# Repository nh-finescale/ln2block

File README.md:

# ln2block

ln2block is the combination of hardware and software to send block messages in a Fremo meeting between two block enabled stations. There are more implementations for this, which can be found at [fremo-block](http://fremo-block.sourceforge.net/) The ln2block variant aims to directly connect Loconet switchpanels to block. First implementation is done with https://smf-modelle.de/ Dr-S2 panels in the Loconet variant. But other implementations such as arduino based or felderblock are possible.

## hardware

The hardware is a adaption of the boards shown [here](http://fremo-block.sourceforge.net/Loconet2Block/index.html) with the following adaptations:
- Schlüesselinterface integrated
- Arduino Nano based to ease programming and debugging
- OLED status display

v5 is a variant which has connections on both ends of the pcb.

v6 is adapted to fit the Strapubox SP2000 (again).

## Getting parts:

Reichelt Shopping Cart for V5 parts: (https://www.reichelt.de/my/1871884). For logging purposes a SSD1306 OLED Display is used. Any I2C variant should work.

## Manuals:

See [the wiki](https://github.com/nh-finescale/ln2block/wiki)

## Software

Software is fully functional for:
* Tf71
* Relaisblock
* Felderblock

### Programming the Arduino

To program the Arduino please use the Arduino IDE.

#### Prerequisites:
* Wire Library (included within IDE): needed for the U8g2 Library
* U8g2 Library: to write text and/or graphic on the OLED display
* LocoNet Library: to send/receive Loconet messages

## Configuration

The ln2block software can be configured through LNCV programming. The values in scope are described at [fremo-block](http://fremo-block.sourceforge.net/Loconet2Block/config.html).
A spreadsheet to calculate the appropriate values for each LNCV is found at https://github.com/nh-finescale/ln2block/tree/main/documentation

This sheet also contains a HEX explanation to translate HEX values shown on the OLED display back into which LNCV are on and off.

## Module connectivity

todo

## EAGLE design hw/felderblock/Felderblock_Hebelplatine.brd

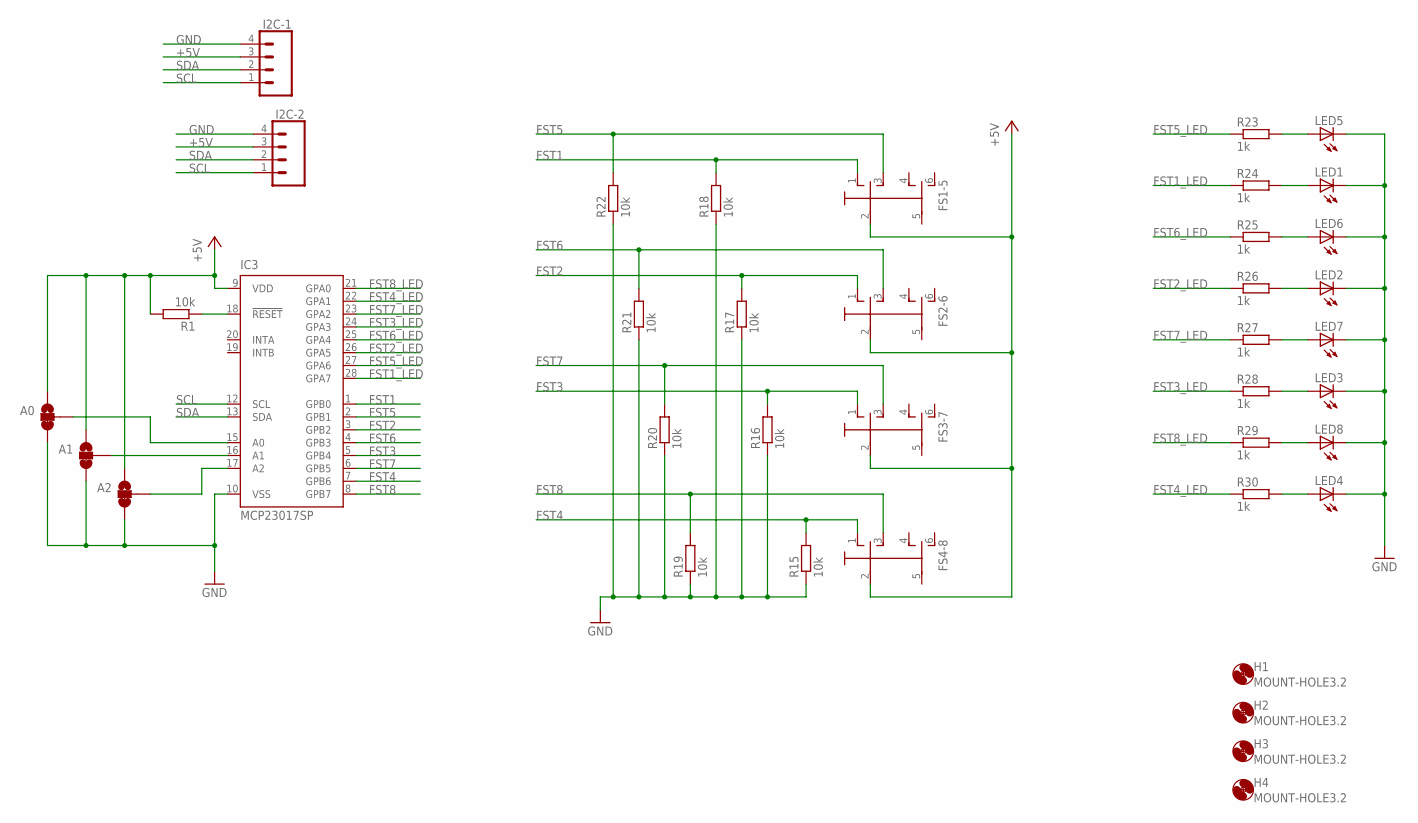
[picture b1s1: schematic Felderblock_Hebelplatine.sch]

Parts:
A0, A1, A2: JUMPER-SMT_3_1-NC_TRACE_SILK; SMT-JUMPER_3_1-NC_TRACE_SILK
FS1-5, FS2-6, FS3-7, FS4-8: SW_2POL_ON-OFF-ONSOLDERPAD; DIL6_LARGE
H1, H2, H3, H4: MOUNT-HOLE3.2; 3,2
I2C-1, I2C-2: CONN_04JST-PTH-VERT; JST-4-PTH-VERT
IC3: MCP23017SP; DIL28-3
LED1, LED2, LED3, LED4, LED5, LED6, LED7, LED8: LED3MM
R1, R15, R16, R17, R18, R19, R20, R21, R22: 10k; 0207/7
R23, R24, R25, R26, R27, R28, R29, R30: 1k; 0207/7

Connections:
+5V: A0.1, A1.1, A2.1, FS1-5.2, FS2-6.2, FS3-7.2, FS4-8.2, I2C-1.3, I2C-2.3, IC3.9 (VDD), R1.2
FST1: FS1-5.1 (O), IC3.1 (GPB0), R18.2
FST1_LED: IC3.28 (GPA7), R24.1
FST2: FS2-6.1 (O), IC3.3 (GPB2), R17.2
FST2_LED: IC3.26 (GPA5), R26.1
FST3: FS3-7.1 (O), IC3.5 (GPB4), R16.2
FST3_LED: IC3.24 (GPA3), R28.1
FST4: FS4-8.1 (O), IC3.7 (GPB6), R15.2
FST4_LED: IC3.22 (GPA1), R30.1
FST5: FS1-5.3 (S), IC3.2 (GPB1), R22.2
FST5_LED: IC3.27 (GPA6), R23.1
FST6: FS2-6.3 (S), IC3.4 (GPB3), R21.2
FST6_LED: IC3.25 (GPA4), R25.1
FST7: FS3-7.3 (S), IC3.6 (GPB5), R20.2
FST7_LED: IC3.23 (GPA2), R27.1
FST8: FS4-8.3 (S), IC3.8 (GPB7), R19.2
FST8_LED: IC3.21 (GPA0), R29.1
GND: A0.3, A1.3, A2.3, I2C-1.4, I2C-2.4, IC3.10 (VSS), LED1.K (C), LED2.K (C), LED3.K (C), LED4.K (C), LED5.K (C), LED6.K (C), LED7.K (C), LED8.K (C), R15.1, R16.1, R17.1, R18.1, R19.1, R20.1, R21.1, R22.1
unnamed: A0.2, IC3.15 (A0)
unnamed: A2.2, IC3.17 (A2)
unnamed: A1.2, IC3.16 (A1)
unnamed: IC3.18 (!RESET), R1.1
unnamed: LED5.A, R23.2
unnamed: LED1.A, R24.2
unnamed: LED6.A, R25.2
unnamed: LED2.A, R26.2
unnamed: LED7.A, R27.2
unnamed: LED3.A, R28.2
unnamed: LED8.A, R29.2
unnamed: LED4.A, R30.2
SCL: I2C-1.1, I2C-2.1, IC3.12 (SCL)
SDA: I2C-1.2, I2C-2.2, IC3.13 (SDA)

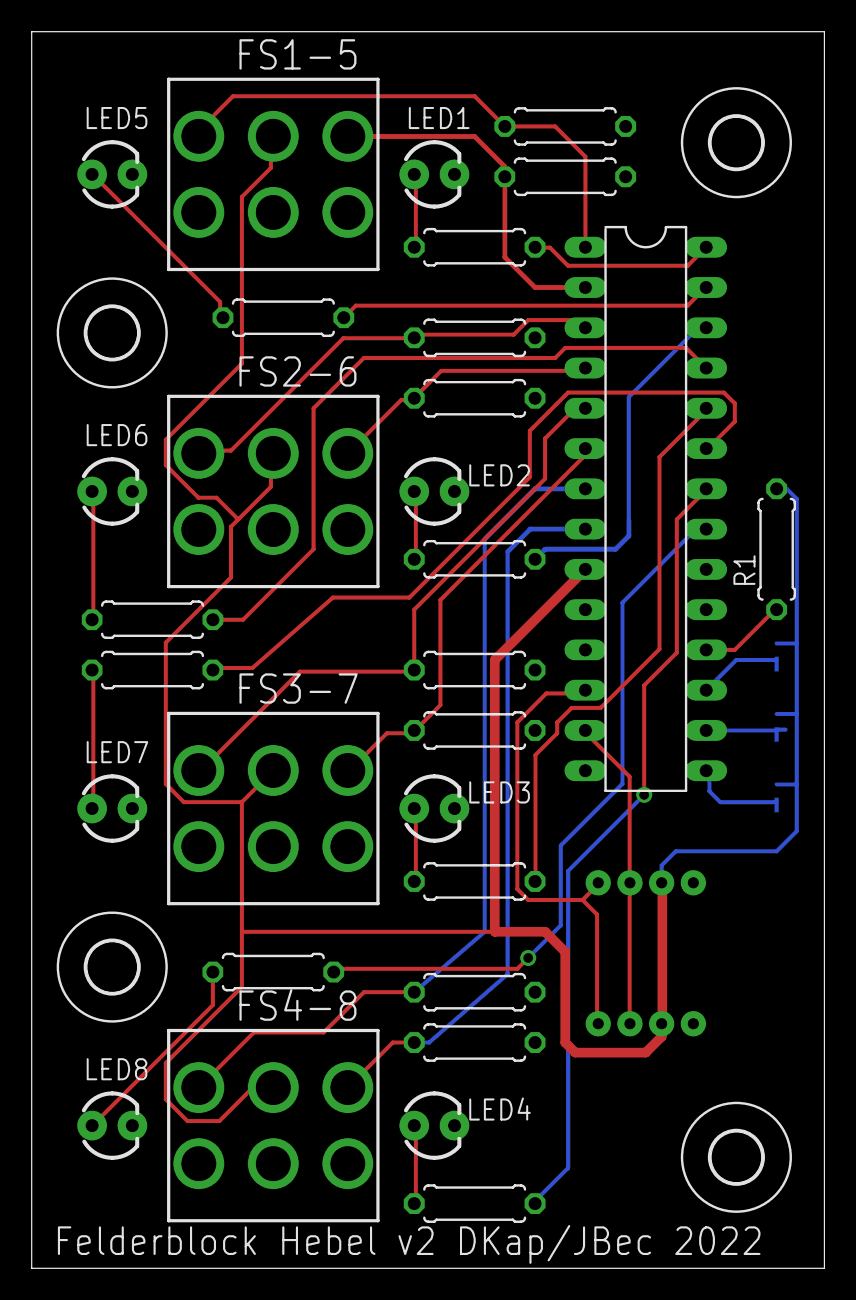
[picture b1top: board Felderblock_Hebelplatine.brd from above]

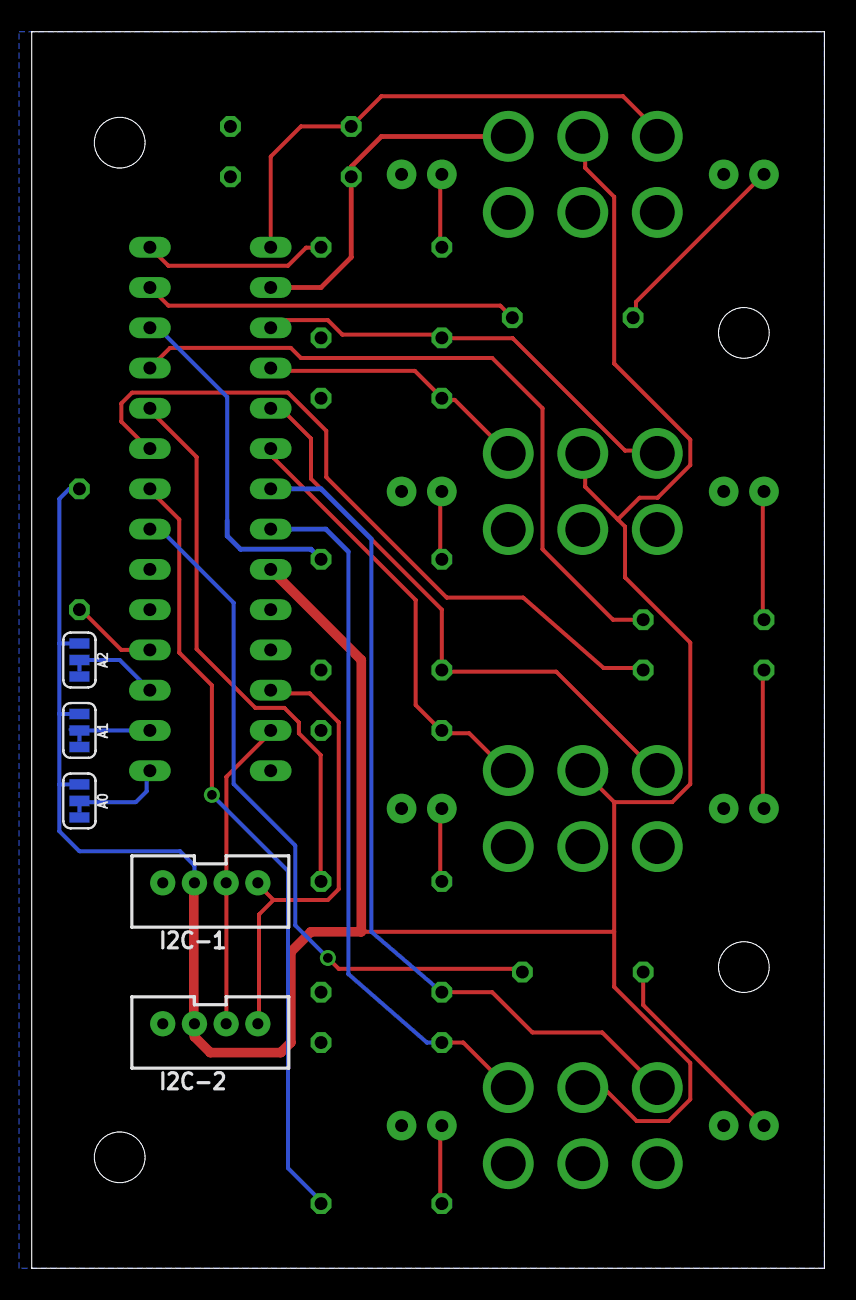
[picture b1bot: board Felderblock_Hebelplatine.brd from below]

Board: 2 copper layers, 50.0 x 78.0 mm, 39 parts (5 on the bottom side), 32 nets.

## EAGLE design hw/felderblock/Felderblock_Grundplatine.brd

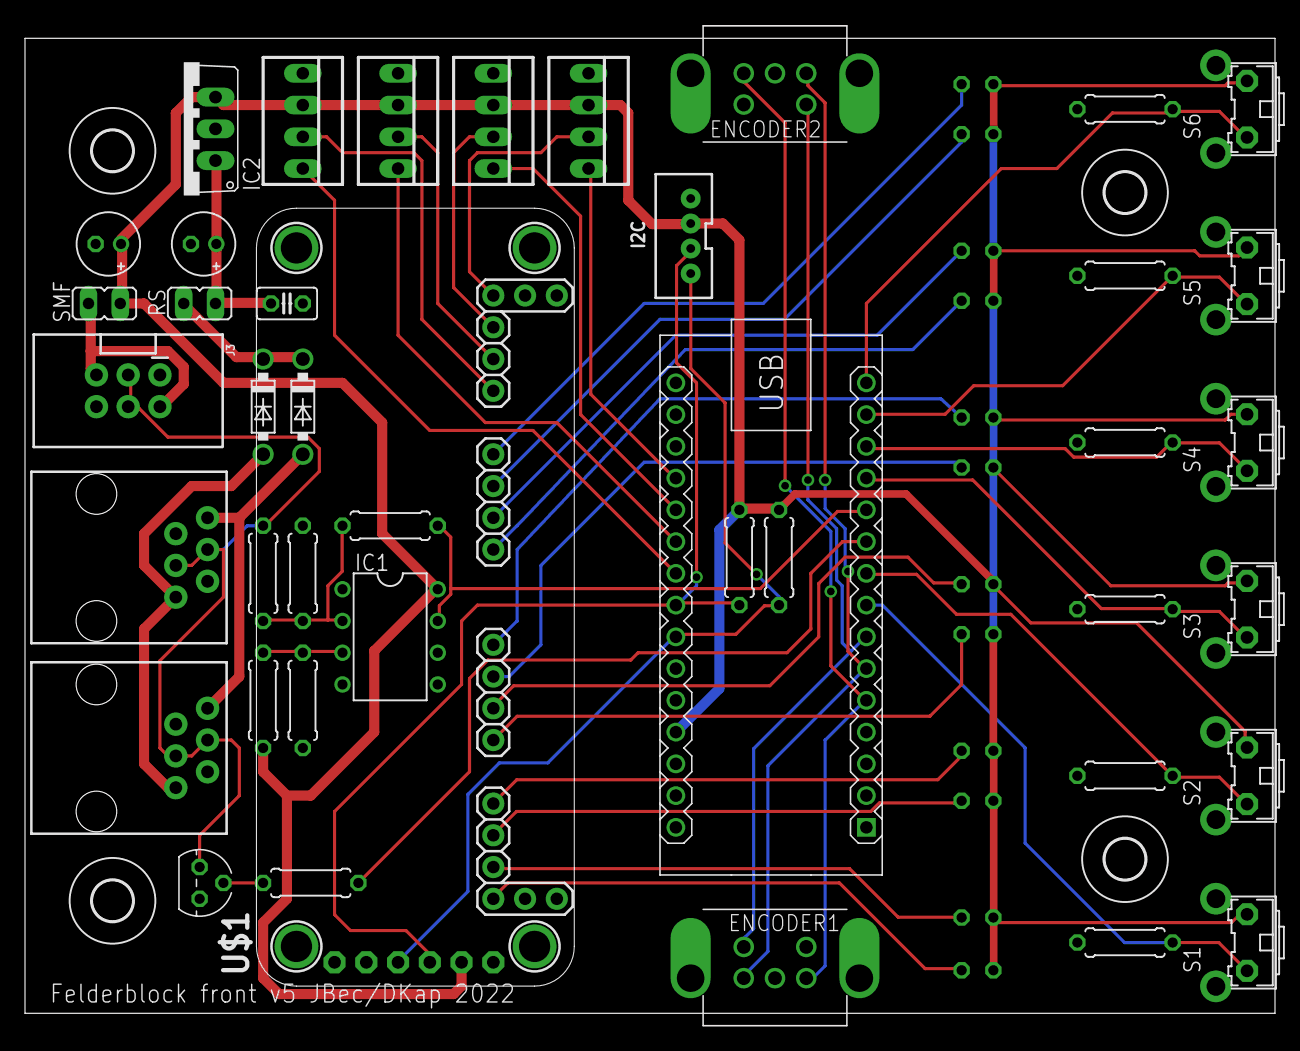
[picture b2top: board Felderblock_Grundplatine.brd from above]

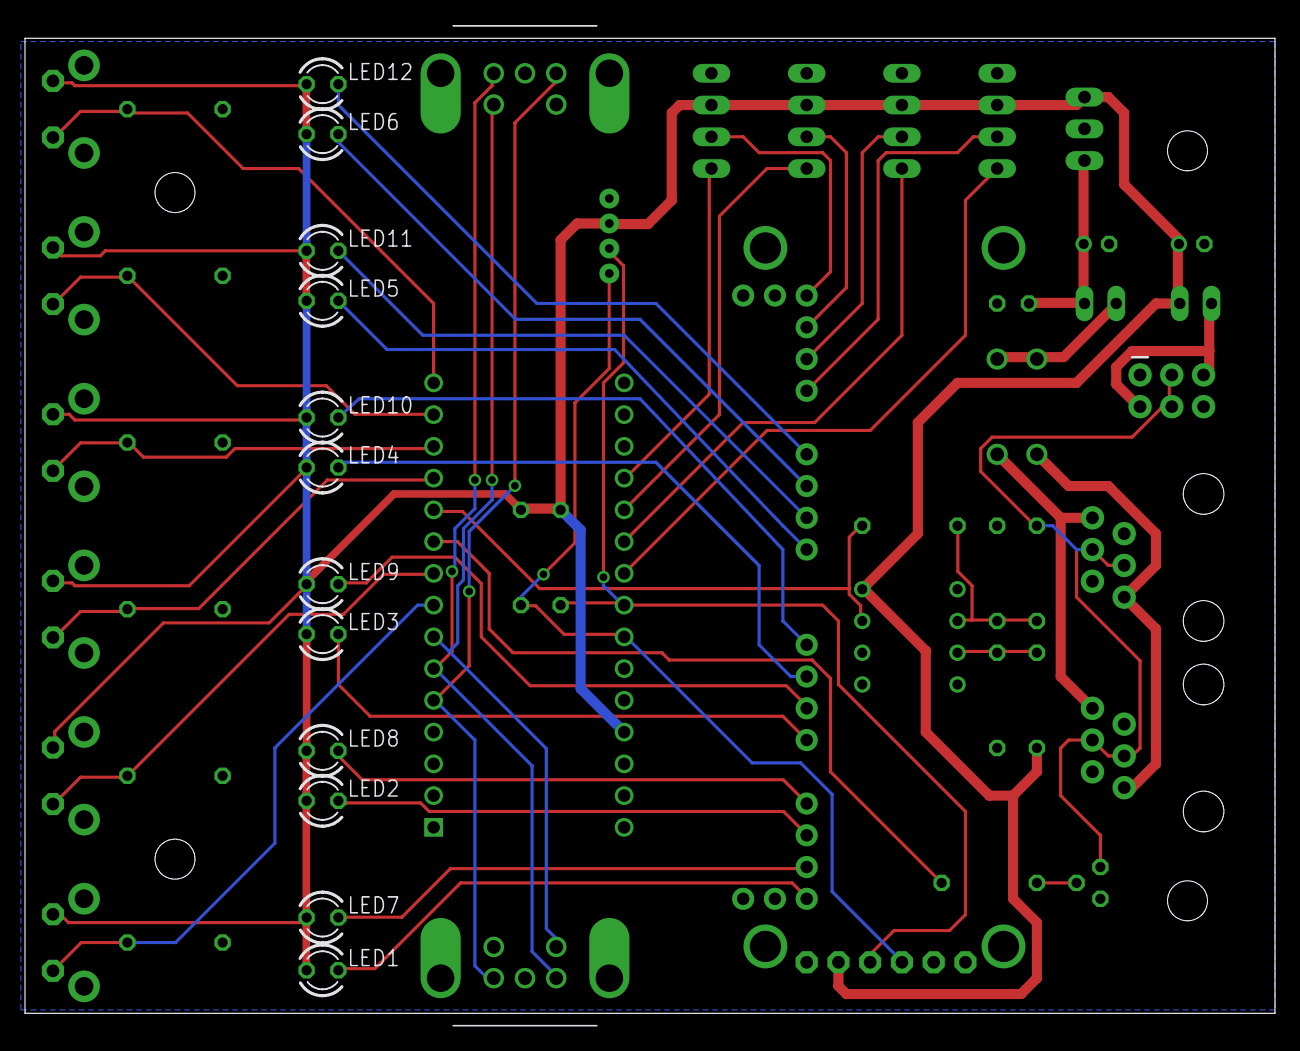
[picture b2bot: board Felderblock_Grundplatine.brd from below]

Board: 2 copper layers, 99.9 x 80.0 mm, 58 parts (12 on the bottom side), 44 nets.

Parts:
C1: 100nF; C025-025X050
C4, C5: 10uF; E2-5
D1, D2: 1N5819-T; DO41-7.6
ENCODER1, ENCODER2: EC11B42
H1, H2, H3, H4: MOUNT-HOLE3.2; 3,2
I2C: JST-4-PTH-VERT
IC1: LM311N; DIL08
IC2: MC78M05CT; TO220V
J1, J2: RJ11; RJ11-6
J3: 2X3-SHROUDED
LED1, LED2, LED3, LED4, LED5, LED6: Red; LED3MM
LED7, LED8, LED9, LED10, LED11, LED12: White; LED3MM
M1: ARDUINO-NANO-3.0
R1, R2: 4K7; 0207/7
R3: 4k7; 0207/7
R4, R5, R7, R8, R9, R10, R18: 10k; 0207/7
R16: 47k; 0207/7
R17: 150k; 0207/7
R19: 22k; 0207/7
R20: 220k; 0207/7
RS: JP1
S1, S2, S3, S4, S5, S6: B3F-31XX
SMF: JP1
T2: BC337; TO92
U$1: ADA9685-STACK
X1: TASTENSPERRE1; 22-23-2041
X2: TASTENSPERRE2; 22-23-2041
X3: SCHL-SPERRE; 22-23-2041
X5: ANSCHALTER; 22-23-2041

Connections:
+5V: C5.+, I2C.3, IC1.8, IC2.3, LED1.A, LED2.A, LED3.A, LED4.A, LED5.A, LED6.A, LED7.A, LED8.A, LED9.A, LED10.A, LED11.A, LED12.A, M1.J2.4, R1.2, R2.2, R18.2, S1.2, S2.2, S3.2, S4.2, S5.2, S6.2, SMF.1, U$1.20, X1.2, X2.2, X3.2, X5.2
AS_LED: U$1.54, X5.3
AS_SW: M1.J2.12, X5.4
BASE: R3.2, T2.2
FELD1_LED_RD: LED1.K, U$1.3
FELD1_LED_WT: LED7.K, U$1.6
FELD1_SW: M1.J1.8, R10.1, S1.1
FELD2_LED_RD: LED2.K, U$1.9
FELD2_LED_WT: LED8.K, U$1.12
FELD2_SW: M1.J1.9, R9.1, S2.1
FELD3_LED_RD: LED3.K, U$1.33
FELD3_LED_WT: LED9.K, U$1.36
FELD3_SW: M1.J1.12, R8.1, S3.1
FELD4_LED_RD: LED4.K, U$1.39
FELD4_LED_WT: LED10.K, U$1.42
FELD4_SW: M1.J1.13, R7.1, S4.1
FELD5_LED_RD: LED5.K, U$1.57
FELD5_LED_WT: LED11.K, U$1.60
FELD5_SW: M1.J1.14, R4.1, S5.1
FELD6_LED_RD: LED6.K, U$1.63
FELD6_LED_WT: LED12.K, U$1.66
FELD6_SW: M1.J1.15, R5.1, S6.1
GND: C1.2, C4.-, C5.-, ENCODER1.C, ENCODER1.E, ENCODER1.GND1, ENCODER1.GND2, ENCODER2.C, ENCODER2.E, ENCODER2.GND1, ENCODER2.GND2, I2C.4, IC1.1, IC1.4, IC2.2, J1.2, J1.5, J2.2, J2.5, J3.1, J3.6, M1.J1.4, M1.J2.2, R4.2, R5.2, R7.2, R8.2, R9.2, R10.2, R17.1, R19.1, T2.1, U$1.1, U$1.24, U$1.52, X1.1, X2.1, X3.1, X5.1
LN_RX: IC1.7, M1.J1.11, R20.1
LN_TX: M1.J1.10, R3.1
LOCONET: J1.3, J1.4, J2.3, J2.4, J3.3, J3.4, R16.2, T2.3
MI_FWD: ENCODER1.B, ENCODER2.B, M1.J1.5
MI_REV: ENCODER1.A, ENCODER2.A, M1.J1.6
MI_SW: ENCODER1.D, ENCODER2.D, M1.J1.7
unnamed: IC1.2, R16.1, R17.2, R20.2
unnamed: D1.C, D2.C, RS.2
unnamed: C1.1, C4.+, IC2.1, RS.1
unnamed: IC1.3, R18.1, R19.2
unnamed: J3.2, J3.5, SMF.2
RS1: D1.A, J1.1, J2.1
RS2: D2.A, J1.6, J2.6
SCHL_SP_LED: U$1.51, X3.3
SCHL_SP_SW: M1.J2.11, X3.4
SCL: I2C.1, M1.J2.7, R1.1, U$1.22
SDA: I2C.2, M1.J2.8, R2.1, U$1.21
TSP1_LED: U$1.45, X1.3
TSP1_SW: M1.J2.9, X1.4
TSP2_LED: U$1.48, X2.3
TSP2_SW: M1.J2.10, X2.4

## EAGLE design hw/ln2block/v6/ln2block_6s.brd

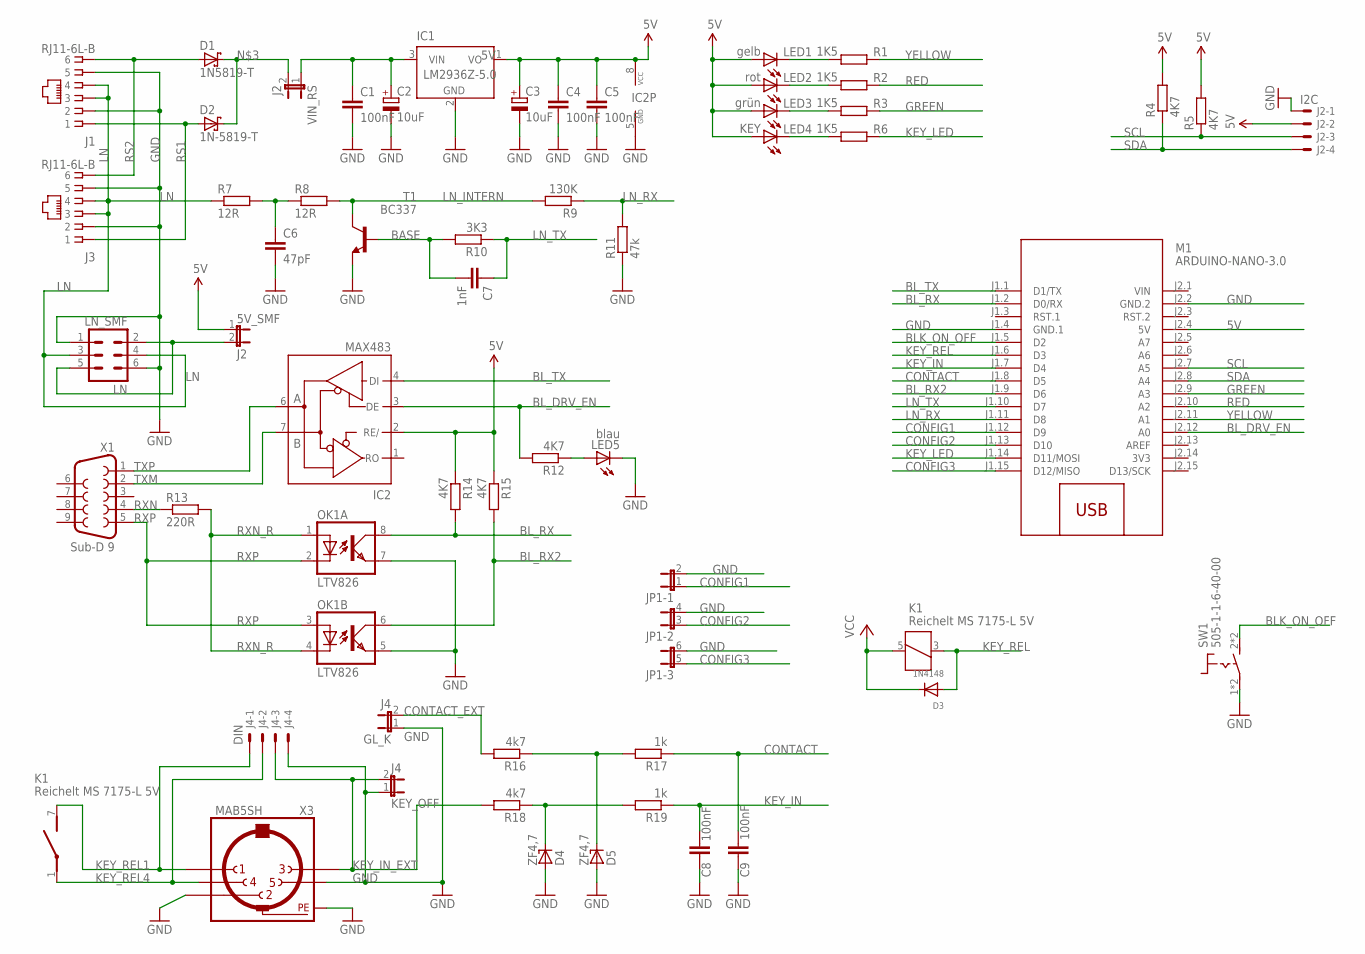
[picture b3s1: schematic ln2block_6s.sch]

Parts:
5V_SMF: J2; JP1
C1, C4, C5, C8, C9: 100nF; C025-025X050
C2, C3: 10uF; E2,5-5
C6: 47pF; C025-024X044
C7: 1nF; C025-025X050
D1: 1N5819-T; DO41-7.6
D2: 1N-5819-T; DO41-7.6
D3: 1N4148; DO-1N4148
D4, D5: ZF4,7; ZDIO-7.5
GL_K: J4; JP1
IC1: LM2936Z-5.0; TO92
IC2: MAX483; DIL08
J1, J3: RJ11-6L-B; RJ11-NO_SHIELD
J2: I2C; 6410-04
J4: DIN; 6410-04
JP1: JP3QE; JP3Q
K1: Reichelt MS 7175-L 5V; MEDER_MS_1A87-75L
KEY_OFF: J4; JP1
LED1: gelb; LED3MM
LED2: rot; LED3MM
LED3: grün; LED3MM
LED4: KEY; LED3MM
LED5: blau; LED3MM
LN: LN_SMF; CON-HARTING-ML_ML6
M1: ARDUINO-NANO-3.0
OK1: LTV826; DIL08
R1, R2, R3, R6: 1K5; 0207/7
R4, R5, R12, R14, R15: 4K7; 0207/7
R7, R8: 12R; 0207/7
R9: 130K; 0207/7
R10: 3K3; 0207/7
R11: 47k; 0207/7
R13: 220R; 0207/7
R16, R18: 4k7; 0207/7
R17, R19: 1k; 0207/7
SW1: 505-1-1-6-40-00; WS-TATV
T1: BC337; TO92
VIN_RS: J2; JP1
X1: Sub-D 9; F09HP
X3: MAB5SH

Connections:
3V3: M1.J2.14 (3V3)
5V: 5V_SMF.1, C3.+, C4.1, C5.1, D3.C, IC1.1 (VO), IC2.2 (RE/), IC2.8 (VCC), J2.2, K1.5, LED1.A, LED2.A, LED3.A, LED4.A, M1.J2.4 (5V), R4.2, R5.2, R14.1, R15.1
BASE: C7.2, R10.2, T1.2 (B)
BLK_ON_OFF: M1.J1.5 (D2), SW1.2 (S), SW1.4 (S)
BL_DRV_EN: IC2.3 (DE), M1.J2.12 (A0), R12.2
BL_RX: M1.J1.2 (D0/RX), OK1.8 (COL), R14.2
BL_RX2: M1.J1.9 (D6), OK1.6 (COL), R15.2
BL_TX: IC2.4 (DI), M1.J1.1 (D1/TX)
CONFIG1: JP1.1, M1.J1.12 (D9)
CONFIG2: JP1.3 (1), M1.J1.13 (D10)
CONFIG3: JP1.5 (1), M1.J1.15 (D12/MISO)
CONTACT: C9.2, M1.J1.8 (D5), R17.1
CONTACT_EXT: GL_K.2, R16.2
GND: C1.2, C2.-, C3.-, C4.2, C5.2, C6.2, C8.1, C9.1, D4.A, D5.A, GL_K.1, IC1.2 (GND), IC2.5 (GND), J1.2, J1.5, J2.1, J3.2, J3.5, J4.4, JP1.2, JP1.4 (2), JP1.6 (2), KEY_OFF.1, LED5.K (C), LN.1, LN.6, M1.J1.4 (GND.1), M1.J2.2 (GND.2), OK1.5 (EMIT), OK1.7 (EMIT), R11.1, SW1.1, SW1.3, T1.1 (E), X3.5, X3.PE, X3.PE1 (PE), X3.PE2 (PE), X3.PE@ (PE)
GREEN: M1.J2.9 (A3), R3.2
KEY_IN: C8.2, M1.J1.7 (D4), R19.1
KEY_IN_EXT: J4.3, KEY_OFF.2, R18.2, X3.3
KEY_LED: M1.J1.14 (D11/MOSI), R6.2
KEY_REL: D3.A, K1.3, M1.J1.6 (D3)
KEY_REL1: J4.1, K1.7 (S), X3.1
KEY_REL4: J4.2, K1.1, X3.4
LN: J1.3, J1.4, J3.3, J3.4, LN.3, LN.4, R7.1
LN_INTERN: R8.2, R9.2, T1.3 (C)
LN_PLUS: C1.1, C2.+, IC1.3 (VIN), VIN_RS.1
LN_RX: M1.J1.11 (D8), R9.1, R11.2
LN_TX: C7.1, M1.J1.10 (D7), R10.1
unnamed: LED4.K (C), R6.1
unnamed: LED5.A, R12.1
unnamed: D1.C, D2.C, VIN_RS.2
unnamed: 5V_SMF.2, LN.2, LN.5
unnamed: D4.C, R18.1, R19.2
unnamed: C6.1, R7.2, R8.1
unnamed: D5.C, R16.1, R17.2
unnamed: LED1.K (C), R1.1
unnamed: LED2.K (C), R2.1
unnamed: LED3.K (C), R3.1
RED: M1.J2.10 (A2), R2.2
RS1: D2.A, J1.1, J3.1
RS2: D1.A, J1.6, J3.6
RXN: R13.1, X1.4
RXN_R: OK1.1 (A), OK1.4 (C), R13.2
RXP: OK1.2 (C), OK1.3 (A), X1.5
SCL: J2.3, M1.J2.7 (A5), R5.1
SDA: J2.4, M1.J2.8 (A4), R4.1
TXM: IC2.7 (B), X1.2
TXP: IC2.6 (A), X1.1
VIN: M1.J2.1 (VIN)
YELLOW: M1.J2.11 (A1), R1.2

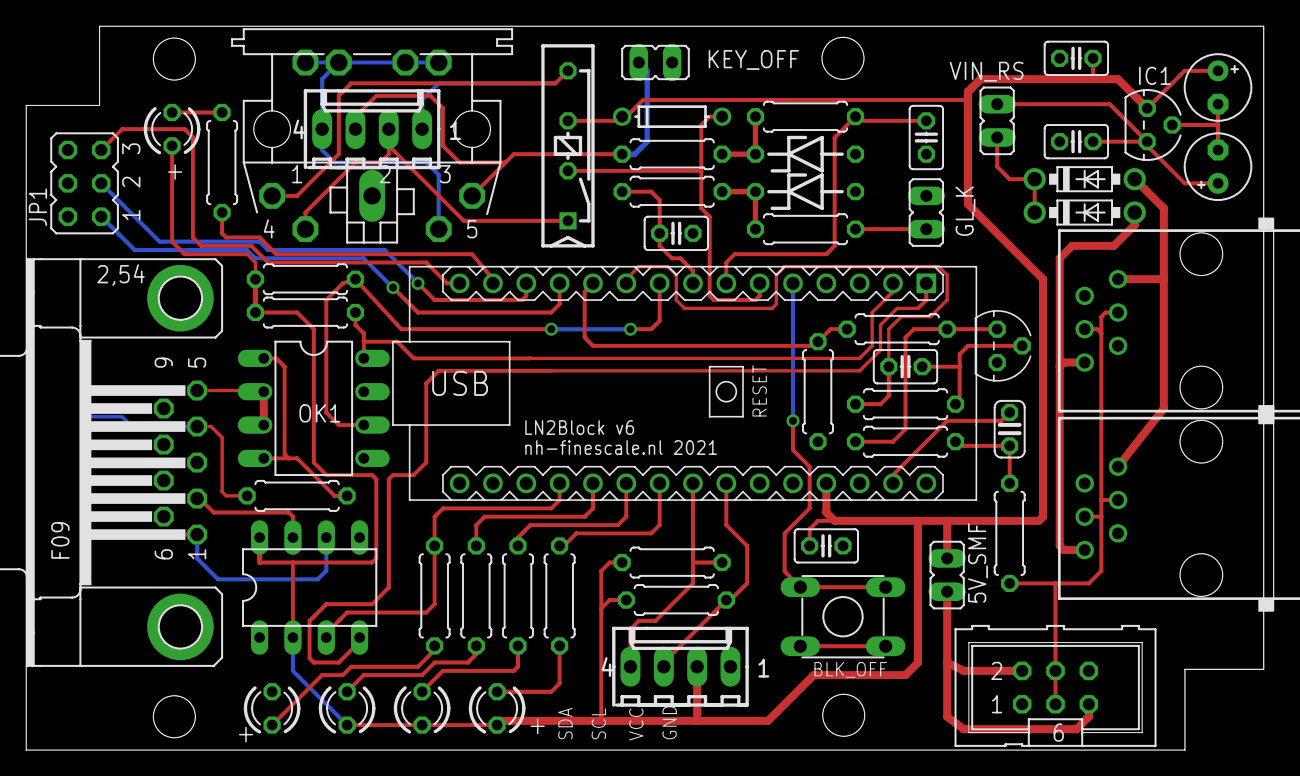
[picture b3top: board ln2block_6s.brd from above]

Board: 2 copper layers, 95.0 x 55.1 mm, 57 parts (0 on the bottom side), 46 nets.

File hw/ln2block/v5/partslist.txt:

Partlist

Exported from ln2block_tht4.brd at 21/05/2021 09:19

EAGLE Version 7.6.0 Copyright (c) 1988-2016 CadSoft

Assembly variant: 

Part     Value                 Package           Library                Position (mm)         Orientation

C1       100nF                 C025-025X050      resistor               (83.5025 57.4675)     R180
C2       10uF                  E2,5-5            resistor               (95.25 55.245)        R90
C3       10uF                  E2,5-5            resistor               (95.25 61.595)        R270
C4       100nF                 C025-025X050      resistor               (83.5025 61.595)      R180
C5       100nF                 C025-025X050      resistor               (73.66 38.4175)       R90
C6       47pF                  C025-024X044      resistor               (74.6125 50.165)      R180
C7       1nF                   C025-025X050      resistor               (74.6125 53.975)      R0
C8       100nF                 C025-025X050      resistor               (56.515 59.055)       R90
C9       100nF                 C025-025X050      resistor               (35.8775 50.165)      R0
D1       1N5819-T              DO41-7.6          diode                  (86.0425 53.6575)     R0
D2                             DO41-7.6          diode                  (86.0425 50.4825)     R0
D3       1N4148                DO-1N4148         adafruit               (29.5275 54.61)       R270
D4       ZF4,7                 ZDIO-7.5          diode                  (48.5775 57.4675)     R0
D5       ZF4,7                 ZDIO-7.5          diode                  (48.5775 53.975)      R0
IC1      LM2936Z-5.0           TO92              national-semiconductor (90.17 58.42)         R270
IC2      MAX483                DIL08             maxim                  (25.4 15.5575)        R0
J1       RJ11-6L-B             RJ11-NO_SHIELD    con-tycoelectronics    (96.52 41.91)         R90
J2       I2C                   6410-04           con-molex              (73.66 10.795)        R180
J3       RJ11-6L-B             RJ11-NO_SHIELD    con-tycoelectronics    (96.52 25.4)          R90
J4       DIN                   6410-04           con-molex              (13.6525 52.07)       R270
JP1      J2                    JP1               jumper                 (56.515 52.3875)      R180
K1       Reichelt MS 7175-L 5V MEDER_MS_1A87-75L sbor                   (25.7175 60.96)       R270
LED1     gelb                  LED3MM            led                    (44.1325 10.16)       R90
LED2     rot                   LED3MM            led                    (49.8475 10.16)       R90
LED3     grün                  LED3MM            led                    (55.5625 10.16)       R90
LED4     rot                   LED3MM            led                    (61.595 10.16)        R90
LED5     blau                  LED3MM            led                    (38.735 10.16)        R90
M1       ARDUINO-NANO-3.0      ARDUINO-NANO-3.0  diy-modules            (55.88 37.1475)       R0
OK1      LTV816S               SMD4              optocoupler            (25.7175 29.21)       R270
OK2      LTV816S               SMD4              optocoupler            (25.7175 35.2425)     R270
R1       1K5                   0207/7            resistor               (44.1325 19.685)      R90
R2       1K5                   0207/7            resistor               (49.8475 19.685)      R90
R3       1K5                   0207/7            resistor               (55.5625 19.685)      R90
R4       4K7                   0207/7            resistor               (74.93 19.685)        R90
R5       4K7                   0207/7            resistor               (72.39 19.685)        R90
R6       1K5                   0207/7            resistor               (61.595 19.685)       R90
R7       12R                   0207/7            resistor               (83.82 33.655)        R90
R8       12R                   0207/7            resistor               (66.675 51.7525)      R180
R9       129k                  0207/7            resistor               (66.675 60.96)        R0
R10      3K3                   0207/7            resistor               (66.675 54.9275)      R0
R11      47k                   0207/7            resistor               (66.675 58.1025)      R180
R12      1K5                   0207/7            resistor               (39.0525 19.685)      R90
R13      220R                  0207/7            resistor               (25.0825 23.8125)     R0
R14      4K7                   0207/7            resistor               (26.035 40.005)       R0
R15      4K7                   0207/7            resistor               (26.035 42.8625)      R0
R16      4k7                   0207/7            resistor               (48.5775 50.8)        R0
R17      1k                    0207/7            resistor               (38.4175 53.975)      R0
R18      4k7                   0207/7            resistor               (38.4175 60.325)      R180
R19      1k                    0207/7            resistor               (48.5775 60.325)      R180
SW1      505-1-1-6-40-00       WS-TATV           fredi                  (87.63 12.7)          R270
T1       BC337                 TO92              transistor             (75.2475 59.3725)     R270
X1       Sub-D 9               F09HP             con-subd               (15.5575 24.4475)     R90
X2       DIN 5 180             MAB5SH            con-hirschmann         (13.335 52.07)        R270

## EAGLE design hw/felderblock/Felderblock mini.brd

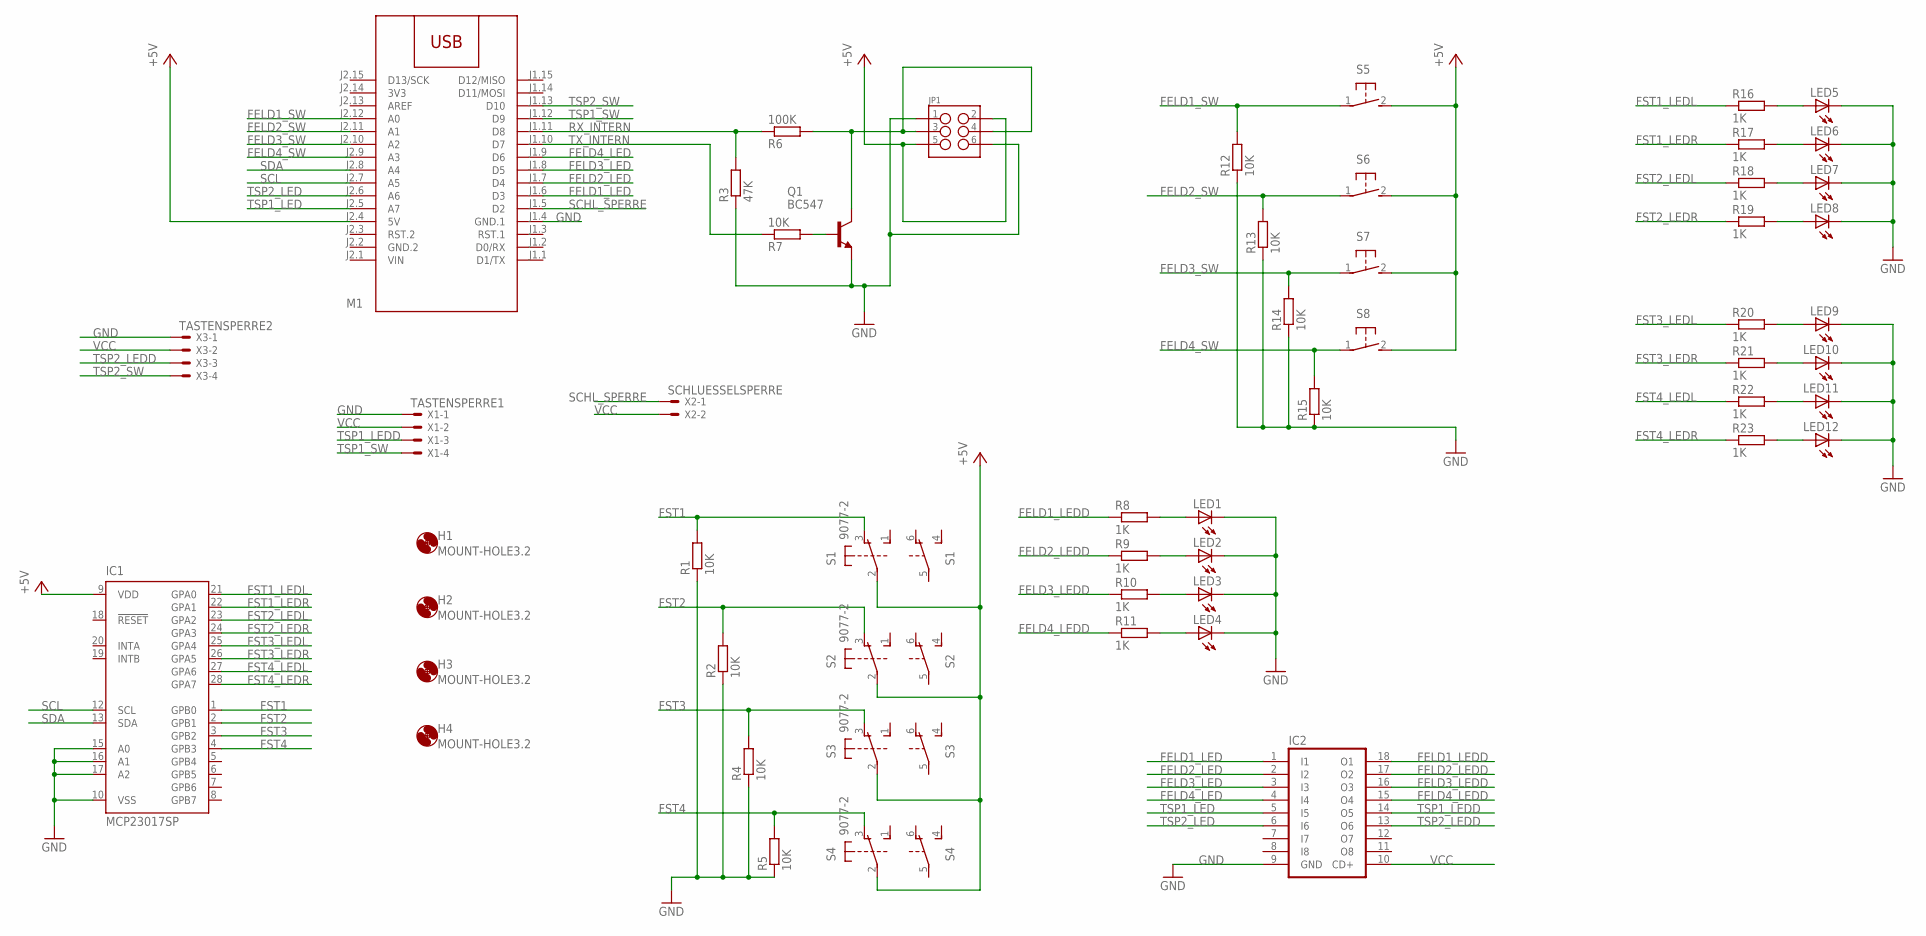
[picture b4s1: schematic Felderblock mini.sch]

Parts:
H1, H2, H3, H4: MOUNT-HOLE3.2; 3,2
IC1: MCP23017SP; DIL28-3
IC2: ULN2803A; DIL18
JP1: M03X2SHROUD; 2X3-SHROUDED
LED1, LED2, LED3, LED4: LED10MM
LED5, LED6, LED7, LED8, LED9, LED10, LED11, LED12: LED5MM
M1: ARDUINO-NANO-3.0
Q1: BC547; TO92
R1, R2, R4, R5, R12, R13, R14, R15: 10K; 0207/7
R3: 47K; R1206
R6: 100K; R1206
R7: 10K; R1206
R8, R9, R10, R11, R16, R17, R18, R19, R20, R21, R22, R23: 1K; 0207/7
S1, S2, S3, S4: 9077-2
S5, S6, S7, S8: 31-XX; B3F-31XX
X1: TASTENSPERRE1; 22-23-2041
X2: SCHLUESSELSPERRE; 22-23-2021
X3: TASTENSPERRE2; 22-23-2041

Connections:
3V3: M1.J2.14 (3V3)
FELD1_LED: IC2.1 (I1), M1.J1.6 (D3)
FELD1_LEDD: IC2.18 (O1), R8.1
FELD1_SW: M1.J2.12 (A0), R12.2, S5.1
FELD2_LED: IC2.2 (I2), M1.J1.7 (D4)
FELD2_LEDD: IC2.17 (O2), R9.1
FELD2_SW: M1.J2.11 (A1), R13.2, S6.1
FELD3_LED: IC2.3 (I3), M1.J1.8 (D5)
FELD3_LEDD: IC2.16 (O3), R10.1
FELD3_SW: M1.J2.10 (A2), R14.2, S7.1
FELD4_LED: IC2.4 (I4), M1.J1.9 (D6)
FELD4_LEDD: IC2.15 (O4), R11.1
FELD4_SW: M1.J2.9 (A3), R15.2, S8.1
FST1: IC1.1 (GPB0), R1.2, S1.3 (O)
FST1_LEDL: IC1.21 (GPA0), R16.1
FST1_LEDR: IC1.22 (GPA1), R17.1
FST2: IC1.2 (GPB1), R2.2, S2.3 (O)
FST2_LEDL: IC1.23 (GPA2), R18.1
FST2_LEDR: IC1.24 (GPA3), R19.1
FST3: IC1.3 (GPB2), R4.2, S3.3 (O)
FST3_LEDL: IC1.25 (GPA4), R20.1
FST3_LEDR: IC1.26 (GPA5), R21.1
FST4: IC1.4 (GPB3), R5.2, S4.3 (O)
FST4_LEDL: IC1.27 (GPA6), R22.1
FST4_LEDR: IC1.28 (GPA7), R23.1
GND: IC1.10 (VSS), IC1.15 (A0), IC1.16 (A1), IC1.17 (A2), IC2.9 (GND), JP1.1, JP1.6, LED1.C, LED2.C, LED3.C, LED4.C, LED5.K (C), LED6.K (C), LED7.K (C), LED8.K (C), LED9.K (C), LED10.K (C), LED11.K (C), LED12.K (C), M1.J1.4 (GND.1), Q1.1 (E), R1.1, R2.1, R3.1, R4.1, R5.1, R12.1, R13.1, R14.1, R15.1, X1.1, X3.1
GND.2: M1.J2.2 (GND.2)
LN: JP1.3, JP1.4, Q1.3 (C), R6.2
unnamed: LED1.A, R8.2
unnamed: LED2.A, R9.2
unnamed: LED3.A, R10.2
unnamed: LED4.A, R11.2
unnamed: Q1.2 (B), R7.2
unnamed: LED5.A, R16.2
unnamed: LED6.A, R17.2
unnamed: LED7.A, R18.2
unnamed: LED8.A, R19.2
unnamed: LED9.A, R20.2
unnamed: LED10.A, R21.2
unnamed: LED11.A, R22.2
unnamed: LED12.A, R23.2
RX_INTERN: M1.J1.11 (D8), R3.2, R6.1
SCHL_SPERRE: M1.J1.5 (D2), X2.1
SCL: IC1.12 (SCL), M1.J2.7 (A5)
SDA: IC1.13 (SDA), M1.J2.8 (A4)
TSP1_LED: IC2.5 (I5), M1.J2.5 (A7)
TSP1_LEDD: IC2.14 (O5), X1.3
TSP1_SW: M1.J1.12 (D9), X1.4
TSP2_LED: IC2.6 (I6), M1.J2.6 (A6)
TSP2_LEDD: IC2.13 (O6), X3.3
TSP2_SW: M1.J1.13 (D10), X3.4
TX_INTERN: M1.J1.10 (D7), R7.1
VCC: IC1.9 (VDD), IC2.10 (CD+), JP1.2, JP1.5, M1.J2.4 (5V), S1.2, S2.2, S3.2, S4.2, S5.2 (S), S6.2 (S), S7.2 (S), S8.2 (S), X1.2, X2.2, X3.2
VIN: M1.J2.1 (VIN)

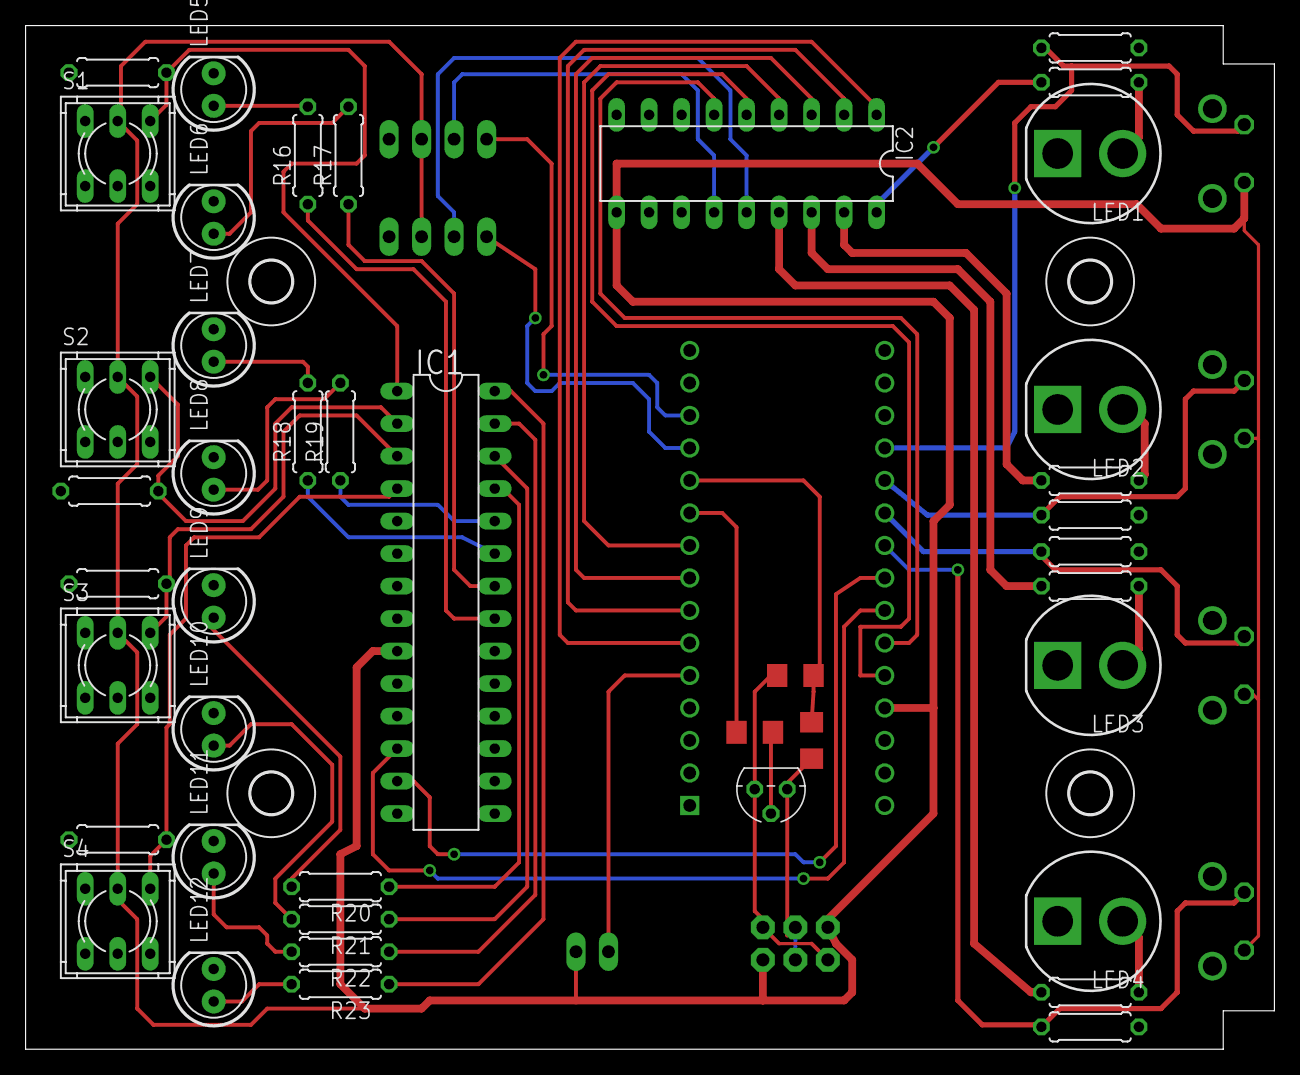
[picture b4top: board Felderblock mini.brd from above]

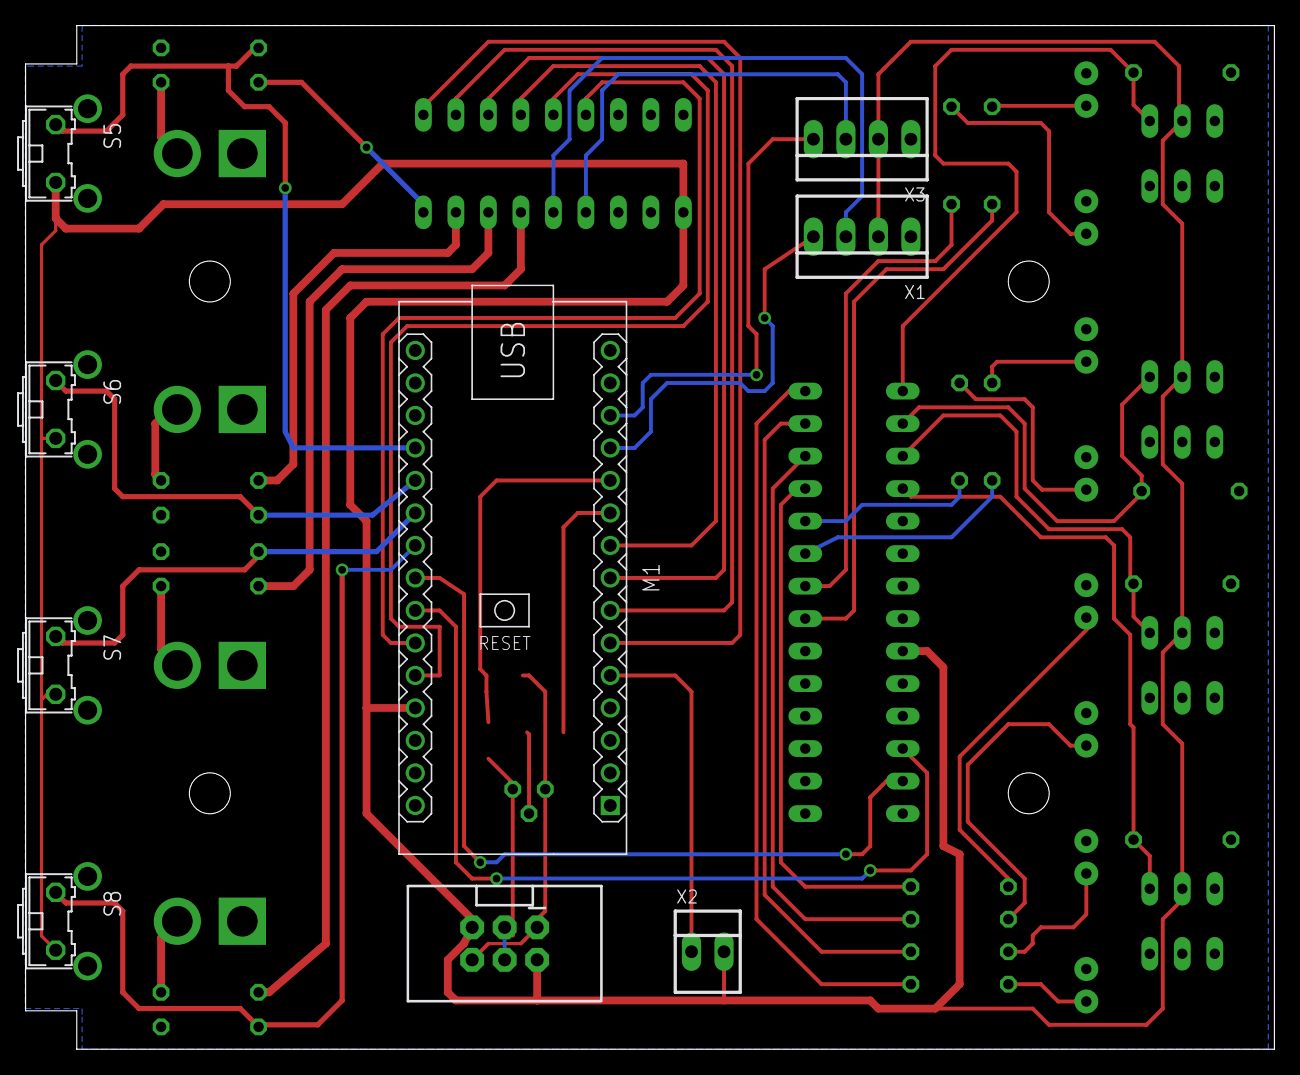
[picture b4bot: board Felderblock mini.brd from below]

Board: 2 copper layers, 97.6 x 80.0 mm, 55 parts (9 on the bottom side), 51 nets.

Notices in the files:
parts and their libraries:
SparkFun-Connectors: Licensing: CC v3.0 Share-Alike You are welcome to use this library for commercial purposes.
diy-modules: Released under the Creative Commons Attribution 4.0 International License: http://creativecommons.org/licenses/by/4.0
